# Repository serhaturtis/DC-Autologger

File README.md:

<div id="top"></div>

<br />
<div align="center">

<h3 align="center">AUTOLOGGER</h3>

  <p align="center">
    A data logging & control board for automobile communications applications.
  </p>
</div>

<!-- WHAT -->
## What?

This is a board for logging and controlling CAN & RS485 communications with an ESP32 module on board for remote connection.

## Why?

Because one of my friends asked me to.

## How?

...

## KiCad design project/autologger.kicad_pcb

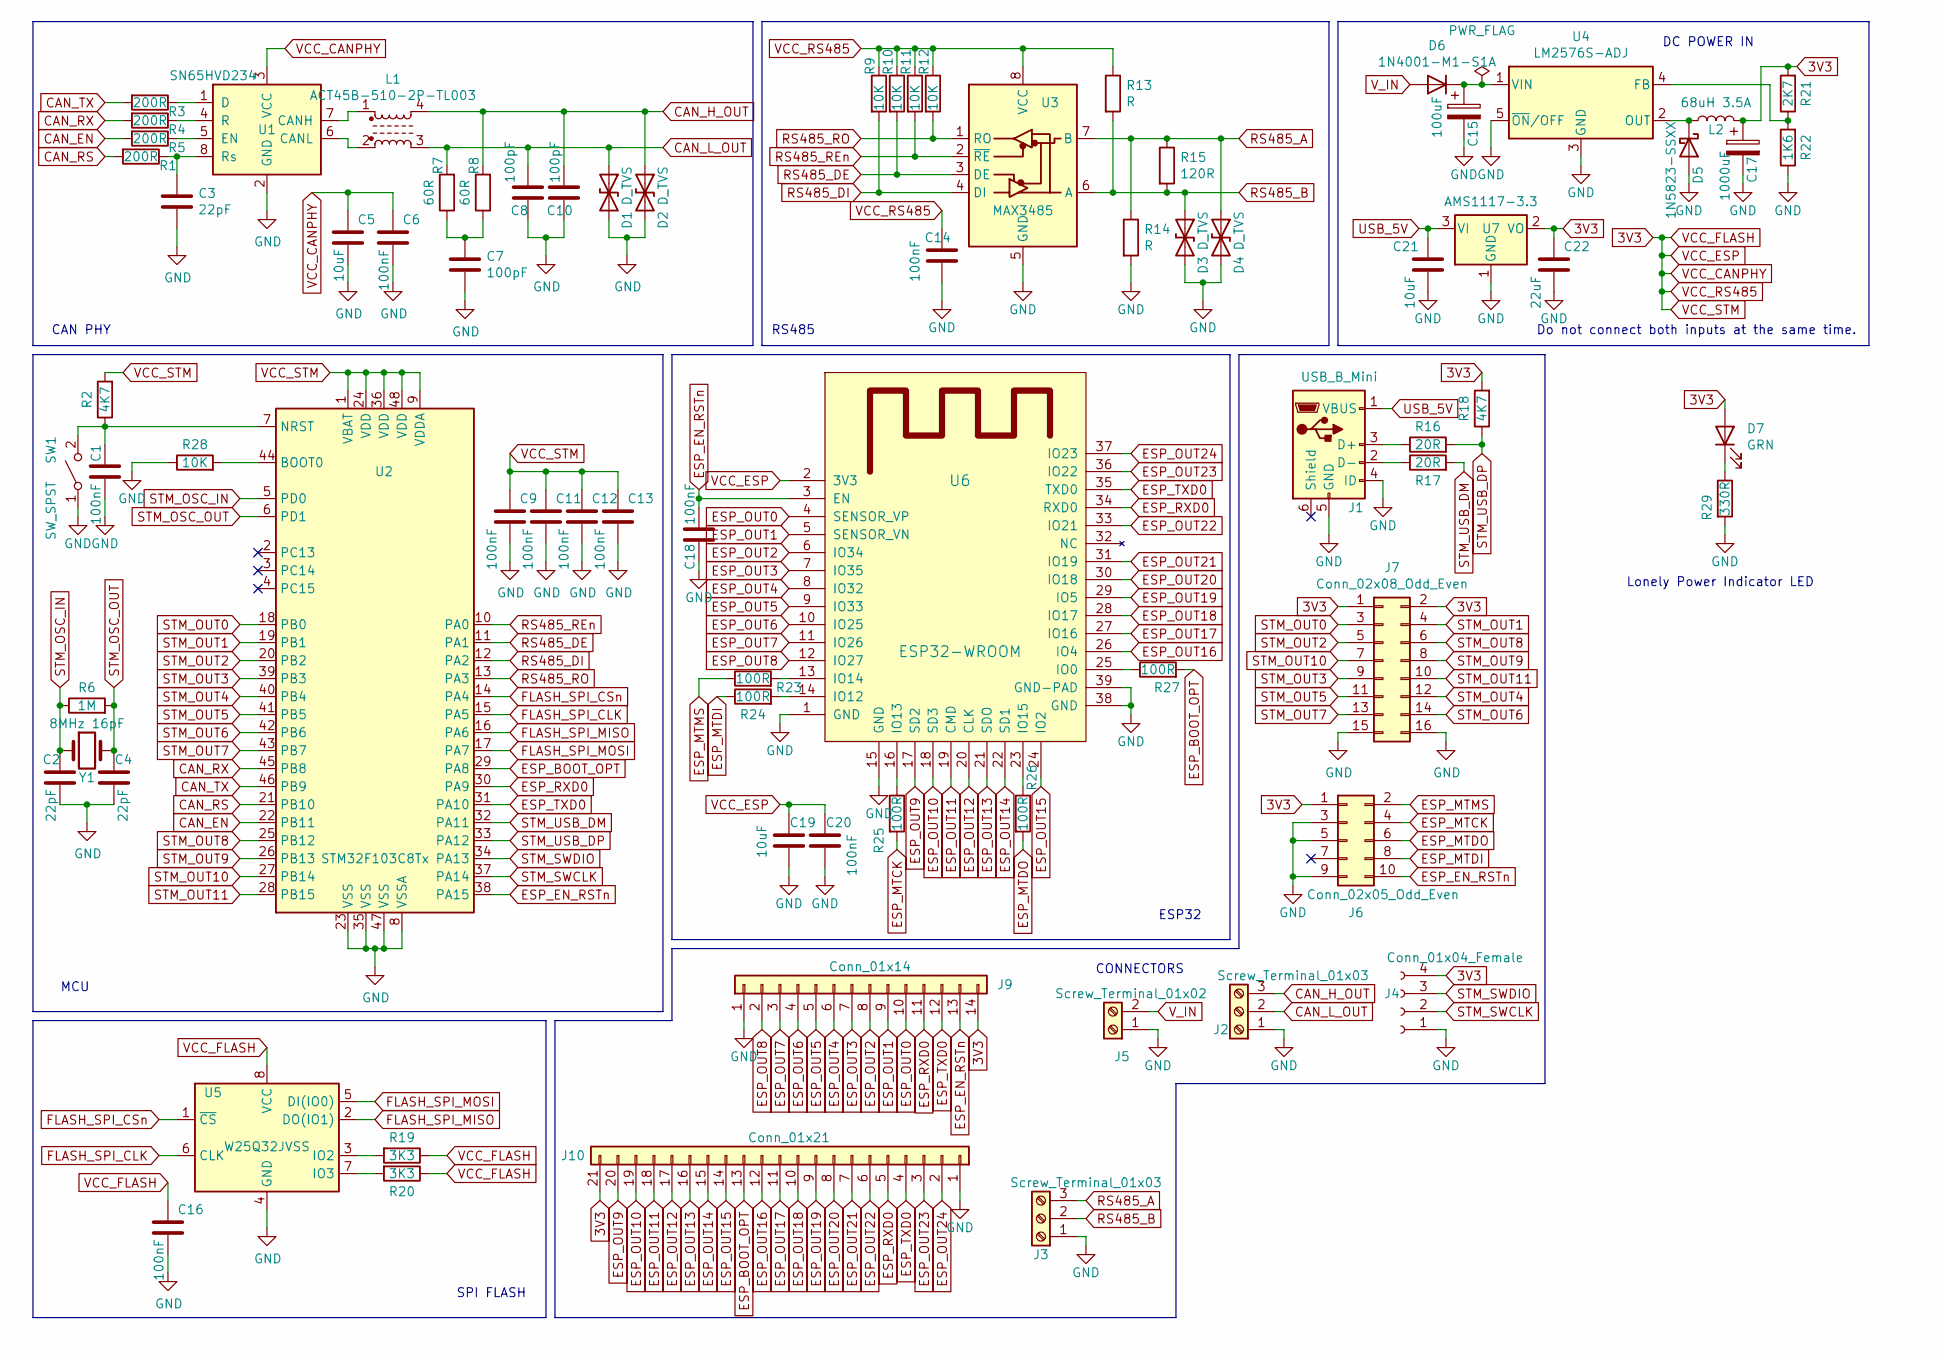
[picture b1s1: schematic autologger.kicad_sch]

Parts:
C1, C6, C9, C11, C12, C13, C14, C16, C18, C20: 100nF; C_0805_2012Metric
C2, C3, C4: 22pF; C_0805_2012Metric
C5, C19, C21: 10uF; C_0805_2012Metric
C7, C8, C10: 100pF; C_0805_2012Metric
C15: 100uF; CP_Elec_8x10
C17: 1000uF; CP_Elec_10x10.5
C22: 22uF; C_0805_2012Metric
D1, D2, D3, D4: D_TVS; D_SMA
D5: 1N5823-SSXX; D_SMA
D6: 1N4001-M1-S1A; D_SMA
D7: GRN; D_0805_2012Metric
J1: USB_B_Mini; USB_Mini-B_Lumberg_2486_01_Horizontal
J2, J3: Screw_Terminal_01x03; TerminalBlock_bornier-3_P5.08mm
J4: Conn_01x04_Female; PinHeader_1x04_P1.27mm_Vertical
J5: Screw_Terminal_01x02; TerminalBlock_bornier-2_P5.08mm
J6: Conn_02x05_Odd_Even; PinHeader_2x05_P1.27mm_Vertical
J7: Conn_02x08_Odd_Even; PinHeader_2x08_P1.27mm_Vertical
J9: Conn_01x14; PinHeader_1x14_P1.27mm_Vertical
J10: Conn_01x21; PinHeader_1x21_P1.27mm_Vertical
L1: ACT45B-510-2P-TL003; L_CommonMode_Wuerth_WE-SL2
L2: 68uH 3.5A; L_12x12mm_H8mm
R1, R3, R4, R5: 200R; R_0805_2012Metric
R2, R18: 4K7; R_0805_2012Metric
R6: 1M; R_0805_2012Metric
R7, R8: 60R; R_0805_2012Metric
R9, R10, R11, R12, R28: 10K; R_0805_2012Metric
R13, R14: R; R_0805_2012Metric
R15: 120R; R_0805_2012Metric
R16, R17: 20R; R_0805_2012Metric
R19, R20: 3K3; R_0805_2012Metric
R21: 2K7; R_0805_2012Metric
R22: 1K6; R_0805_2012Metric
R23, R24, R25, R26, R27: 100R; R_0805_2012Metric
R29: 330R; R_0805_2012Metric
SW1: SW_SPST; SW_SPST_TL3342
U1: SN65HVD234; SOIC-8_3.9x4.9mm_P1.27mm
U2: STM32F103C8Tx; LQFP-48_7x7mm_P0.5mm
U3: MAX3485; SO-8_5.3x6.2mm_P1.27mm
U4: LM2576S-ADJ; TO-263-5_TabPin3
U5: W25Q32JVSS; SOIC-8_5.23x5.23mm_P1.27mm
U6: ESP32-WROOM
U7: AMS1117-3.3; SOT-223-3_TabPin2
Y1: 8MHz 16pF; Crystal_SMD_HC49-SD

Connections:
3V3: C5.1, C6.1, C9.1, C11.1, C12.1, C13.1, C14.1, C16.1, C17.1, C19.1, C20.1, C22.1, D7.2 (A), J4.4, J6.1, J7.1, J7.2, J9.14, J10.21, L2.2, R2.2, R9.1, R10.1, R11.1, R12.1, R13.1, R18.2, R19.1, R20.1, R21.2, U1.3 (VCC), U2.1 (VBAT), U2.9 (VDDA), U2.24 (VDD), U2.36 (VDD), U2.48 (VDD), U3.8 (VCC), U5.8 (VCC), U6.2 (3V3), U7.2 (VO)
CAN_EN: R5.2, U2.22 (PB11)
CAN_H_OUT: C10.1, D2.1 (A1), J2.3, L1.4, R8.2
CAN_L_OUT: C8.1, D1.1 (A1), J2.2, L1.3, R7.2
CAN_RS: R1.2, U2.21 (PB10)
CAN_RX: R4.2, U2.45 (PB8)
CAN_TX: R3.2, U2.46 (PB9)
ESP_BOOT_OPT: J10.13, R27.2, U2.29 (PA8)
ESP_EN_RSTn: C18.1, J6.10, J9.13, U2.38 (PA15), U6.3 (EN)
ESP_MTCK: J6.4, R25.2
ESP_MTDI: J6.8, R24.1
ESP_MTDO: J6.6, R26.2
ESP_MTMS: J6.2, R23.1
ESP_OUT0: J9.10, U6.4 (SENSOR_VP)
ESP_OUT1: J9.9, U6.5 (SENSOR_VN)
ESP_OUT2: J9.8, U6.6 (IO34)
ESP_OUT3: J9.7, U6.7 (IO35)
ESP_OUT4: J9.6, U6.8 (IO32)
ESP_OUT5: J9.5, U6.9 (IO33)
ESP_OUT6: J9.4, U6.10 (IO25)
ESP_OUT7: J9.3, U6.11 (IO26)
ESP_OUT8: J9.2, U6.12 (IO27)
ESP_OUT9: J10.20, U6.17 (SD2)
ESP_OUT10: J10.19, U6.18 (SD3)
ESP_OUT11: J10.18, U6.19 (CMD)
ESP_OUT12: J10.17, U6.20 (CLK)
ESP_OUT13: J10.16, U6.21 (SDO)
ESP_OUT14: J10.15, U6.22 (SD1)
ESP_OUT15: J10.14, U6.24 (IO2)
ESP_OUT16: J10.12, U6.26 (IO4)
ESP_OUT17: J10.11, U6.27 (IO16)
ESP_OUT18: J10.10, U6.28 (IO17)
ESP_OUT19: J10.9, U6.29 (IO5)
ESP_OUT20: J10.8, U6.30 (IO18)
ESP_OUT21: J10.7, U6.31 (IO19)
ESP_OUT22: J10.6, U6.33 (IO21)
ESP_OUT23: J10.3, U6.36 (IO22)
ESP_OUT24: J10.2, U6.37 (IO23)
ESP_RXD0: J9.11, J10.5, U2.30 (PA9), U6.34 (RXD0)
ESP_TXD0: J9.12, J10.4, U2.31 (PA10), U6.35 (TXD0)
FLASH_SPI_CLK: U2.15 (PA5), U5.6 (CLK)
FLASH_SPI_CSn: U2.14 (PA4), U5.1 (~CS)
FLASH_SPI_MISO: U2.16 (PA6), U5.2 (DO(IO1))
FLASH_SPI_MOSI: U2.17 (PA7), U5.5 (DI(IO0))
GND: C1.2, C2.2, C3.2, C4.2, C5.2, C6.2, C7.2, C8.2, C9.2, C10.2, C11.2, C12.2, C13.2, C14.2, C15.2, C16.2, C17.2, C18.2, C19.2, C20.2, C21.2, C22.2, D1.2 (A2), D2.2 (A2), D3.2 (A2), D4.2 (A2), D5.2 (A), J1.4 (ID), J1.5 (GND), J2.1, J3.1, J4.1, J5.1, J6.3, J6.5, J6.9, J7.15, J7.16, J9.1, J10.1, R14.2, R22.1, R28.1, R29.2, SW1.1 (A), U1.2 (GND), U2.8 (VSSA), U2.23 (VSS), U2.35 (VSS), U2.47 (VSS), U3.5 (GND), U4.3 (GND), U4.5 (~ON/OFF), U5.4 (GND), U6.1 (GND), U6.15 (GND), U6.38 (GND), U6.39 (GND-PAD), U7.1 (GND)
unnamed: C1.1, R2.1, SW1.2 (B), U2.7 (NRST)
unnamed: C3.1, R1.1, U1.8 (Rs)
unnamed: C7.1, R7.1, R8.1
unnamed: C15.1, D6.1 (K), U4.1 (VIN)
unnamed: D5.1 (K), L2.1, U4.2 (OUT)
unnamed: D7.1 (K), R29.1
unnamed: J1.2 (D-), R17.1
unnamed: J1.3 (D+), R16.1
unnamed: L1.1, U1.7 (CANH)
unnamed: L1.2, U1.6 (CANL)
unnamed: R3.1, U1.1 (D)
unnamed: R4.1, U1.4 (R)
unnamed: R5.1, U1.5 (EN)
unnamed: R19.2, U5.3 (IO2)
unnamed: R20.2, U5.7 (IO3)
unnamed: R21.1, R22.2, U4.4 (FB)
unnamed: R23.2, U6.13 (IO14)
unnamed: R24.2, U6.14 (IO12)
unnamed: R25.1, U6.16 (IO13)
unnamed: R26.1, U6.23 (IO15)
unnamed: R27.1, U6.25 (IO0)
unnamed: R28.2, U2.44 (BOOT0)
RS485_A: D4.1 (A1), J3.3, R14.1, R15.1, U3.7 (B)
RS485_B: D3.1 (A1), J3.2, R13.2, R15.2, U3.6 (A)
RS485_DE: R10.2, U2.11 (PA1), U3.3 (DE)
RS485_DI: R9.2, U2.12 (PA2), U3.4 (DI)
RS485_REn: R11.2, U2.10 (PA0), U3.2 (~RE)
RS485_RO: R12.2, U2.13 (PA3), U3.1 (RO)
STM_OSC_IN: C2.1, R6.1, U2.5 (PD0), Y1.1
STM_OSC_OUT: C4.1, R6.2, U2.6 (PD1), Y1.2
STM_OUT0: J7.3, U2.18 (PB0)
STM_OUT1: J7.4, U2.19 (PB1)
STM_OUT2: J7.5, U2.20 (PB2)
STM_OUT3: J7.9, U2.39 (PB3)
STM_OUT4: J7.12, U2.40 (PB4)
STM_OUT5: J7.11, U2.41 (PB5)
STM_OUT6: J7.14, U2.42 (PB6)
STM_OUT7: J7.13, U2.43 (PB7)
STM_OUT8: J7.6, U2.25 (PB12)
STM_OUT9: J7.8, U2.26 (PB13)
STM_OUT10: J7.7, U2.27 (PB14)
STM_OUT11: J7.10, U2.28 (PB15)
STM_SWCLK: J4.2, U2.37 (PA14)
STM_SWDIO: J4.3, U2.34 (PA13)
STM_USB_DM: R17.2, U2.32 (PA11)
STM_USB_DP: R16.2, R18.1, U2.33 (PA12)
USB_5V: C21.1, J1.1 (VBUS), U7.3 (VI)
V_IN: D6.2 (A), J5.2

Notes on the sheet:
DC POWER IN
CAN PHY
SPI FLASH
MCU
RS485
Do not connect both inputs at the same time.
ESP32
Lonely Power Indicator LED
CONNECTORS

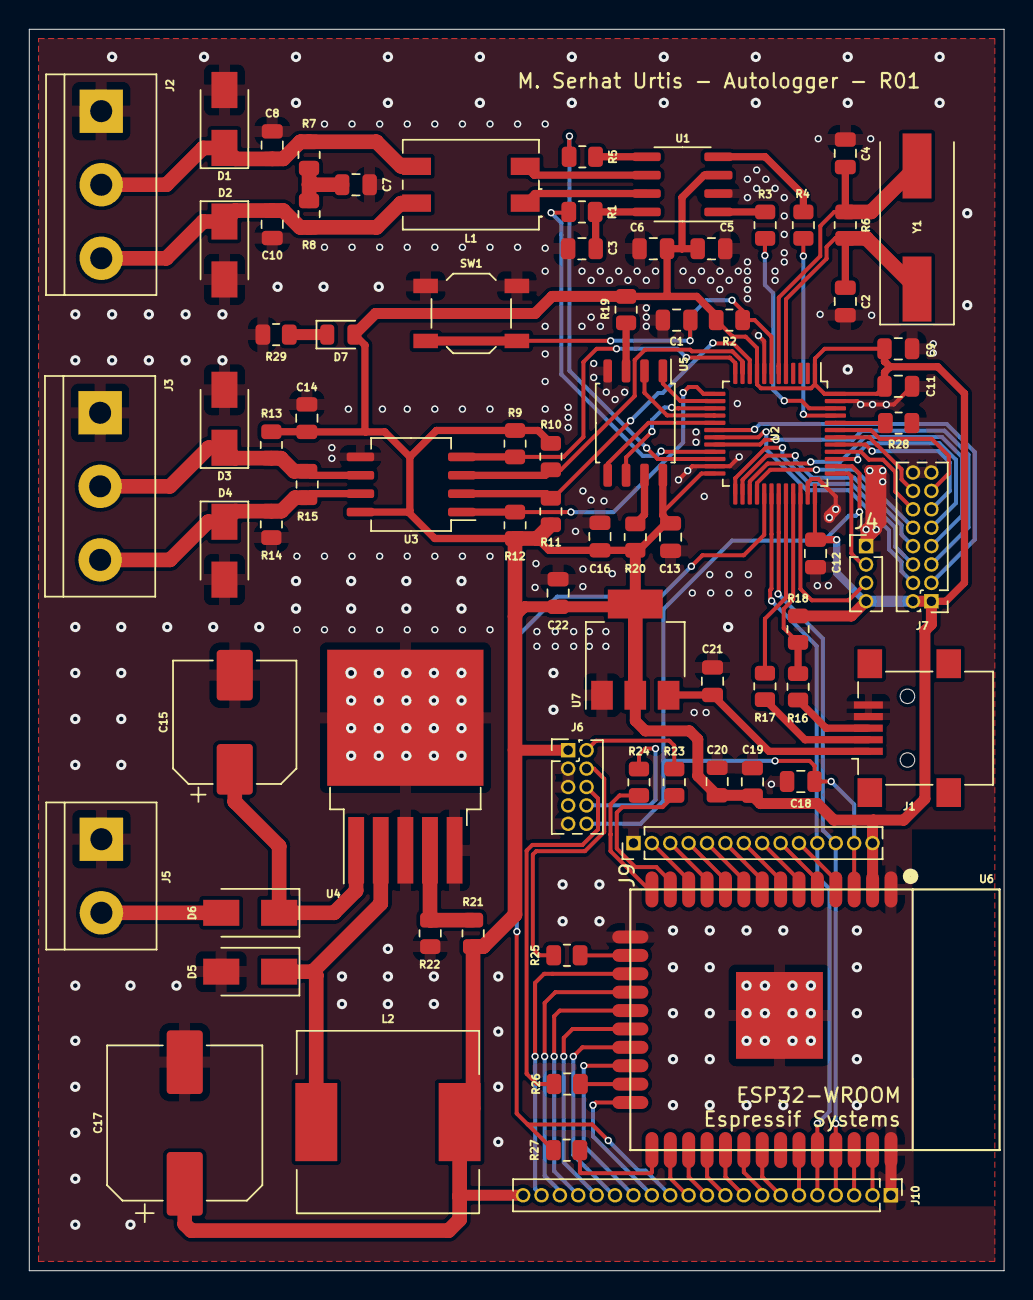
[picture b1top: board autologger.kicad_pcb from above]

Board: 2 copper layers, 67.3 x 85.7 mm, 78 parts (0 on the bottom side), 93 nets.

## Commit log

2022-01-12 Removed backup files
2022-01-12 cropped images
2022-01-12 fixed front image
